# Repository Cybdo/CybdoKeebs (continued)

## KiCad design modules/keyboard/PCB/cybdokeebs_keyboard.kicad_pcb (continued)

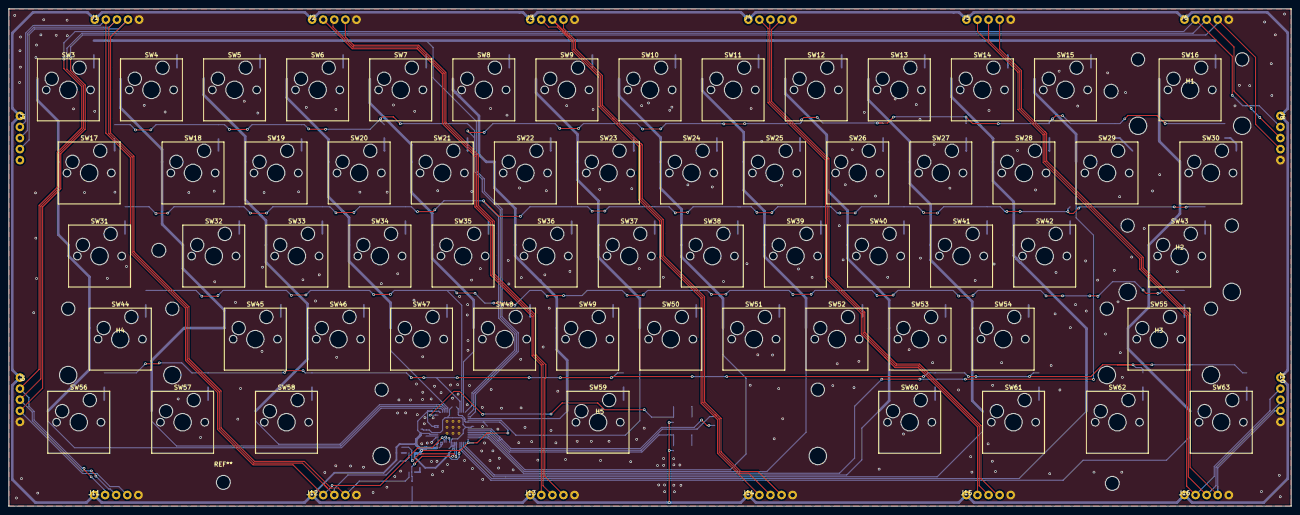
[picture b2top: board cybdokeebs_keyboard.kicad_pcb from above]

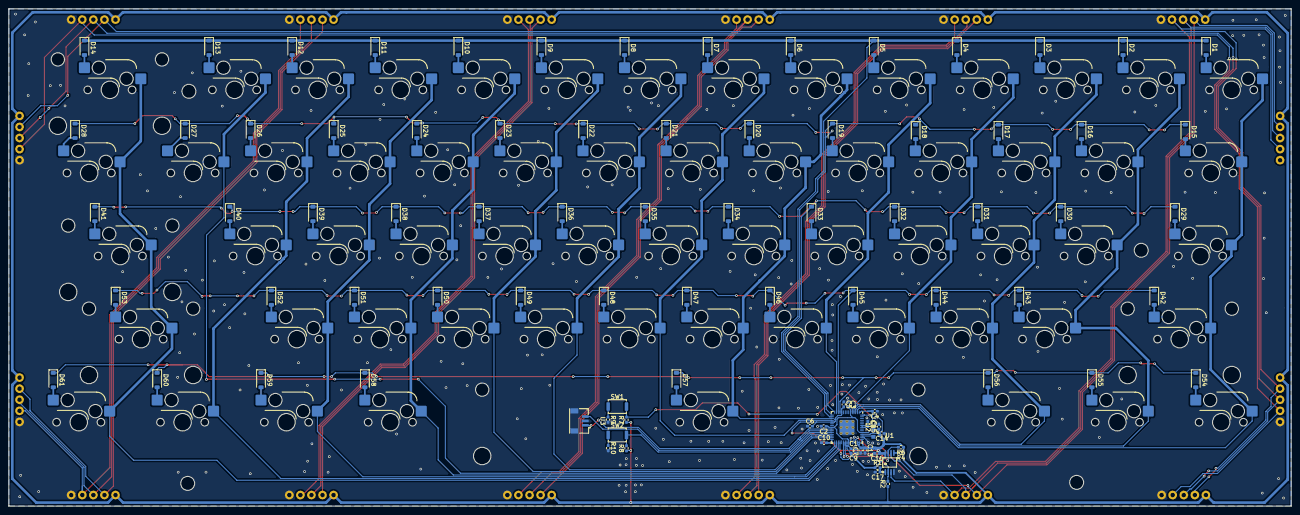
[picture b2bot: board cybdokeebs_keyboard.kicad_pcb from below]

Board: 2 copper layers, 294.0 x 114.0 mm, 172 parts (90 on the bottom side), 112 nets.

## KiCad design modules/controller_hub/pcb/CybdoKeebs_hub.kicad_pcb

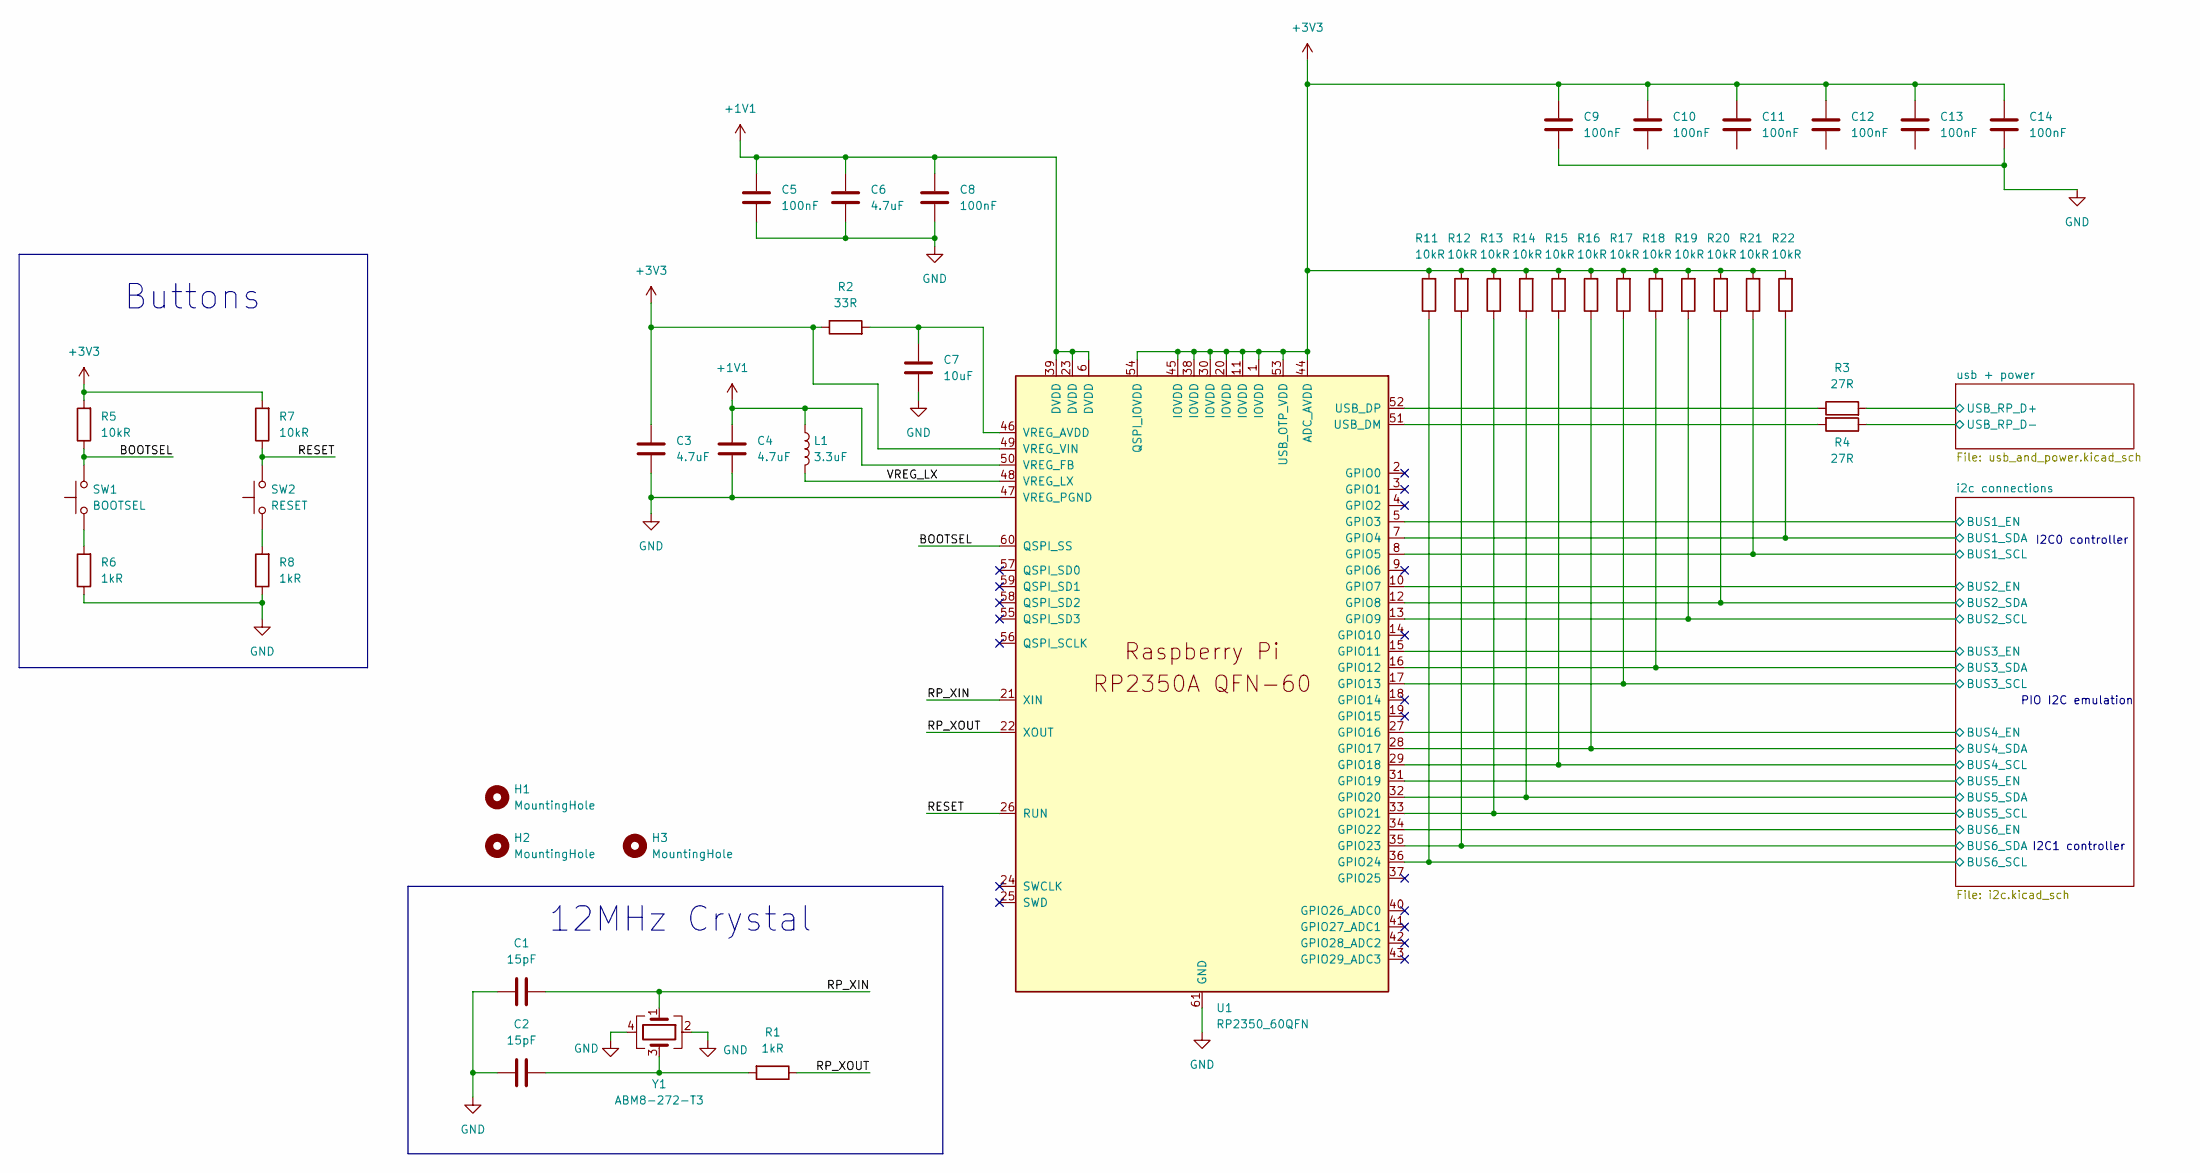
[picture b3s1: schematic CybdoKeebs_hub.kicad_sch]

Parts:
C1, C2: 15pF; C_0402_1005Metric_Pad0.74x0.62mm_HandSolder
C3, C4, C6: 4.7uF; C_0402_1005Metric_Pad0.74x0.62mm_HandSolder
C5, C8, C9, C10, C11, C12, C13, C14: 100nF; C_0402_1005Metric_Pad0.74x0.62mm_HandSolder
C7: 10uF; C_0402_1005Metric_Pad0.74x0.62mm_HandSolder
H1, H2, H3: MountingHole; MountingHole_3.2mm_M3
L1: 3.3uF; INDC1608X95N
R1, R6, R8: 1kR; R_0402_1005Metric_Pad0.72x0.64mm_HandSolder
R2: 33R; R_0402_1005Metric_Pad0.72x0.64mm_HandSolder
R3, R4: 27R; R_0402_1005Metric_Pad0.72x0.64mm_HandSolder
R5, R7, R11, R12, R13, R14, R15, R16, R17, R18, R19, R20, R21, R22: 10kR; R_0402_1005Metric_Pad0.72x0.64mm_HandSolder
SW1: BOOTSEL; SW_Push_SPST_NO_Alps_SKRK
SW2: RESET; SW_Push_SPST_NO_Alps_SKRK
U1: RP2350_60QFN; RP2350-QFN-60-1EP_7x7_P0.4mm_EP3.4x3.4mm_ThermalVias
Y1: ABM8-272-T3; Crystal_SMD_Abracon_ABM8G-4Pin_3.2x2.5mm

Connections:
+1V1: C4.1, C5.1, C6.1, C8.1, L1.1, U1.6 (DVDD), U1.23 (DVDD), U1.39 (DVDD), U1.50 (VREG_FB)
+3V3: C3.1, C9.1, C10.1, C11.1, C12.1, C13.1, C14.1, R2.1, R5.2, R7.2, R11.2, R12.2, R13.2, R14.2, R15.2, R16.2, R17.2, R18.2, R19.2, R20.2, R21.2, R22.2, U1.1 (IOVDD), U1.11 (IOVDD), U1.20 (IOVDD), U1.30 (IOVDD), U1.38 (IOVDD), U1.44 (ADC_AVDD), U1.45 (IOVDD), U1.49 (VREG_VIN), U1.53 (USB_OTP_VDD), U1.54 (QSPI_IOVDD); also elsewhere on the board
/BOOTSEL: R5.1, SW1.2, U1.60 (QSPI_SS)
/RESET: R7.1, SW2.2, U1.26 (RUN)
/RP_XIN: C1.2, U1.21 (XIN), Y1.1
/RP_XOUT: R1.1, U1.22 (XOUT)
/VREG_LX: L1.2, U1.48 (VREG_LX)
/i2c connections/BUS1_EN: U1.5 (GPIO3); also elsewhere on the board
/i2c connections/BUS1_SCL: R21.1, U1.8 (GPIO5); also elsewhere on the board
/i2c connections/BUS1_SDA: R22.1, U1.7 (GPIO4); also elsewhere on the board
/i2c connections/BUS2_EN: U1.10 (GPIO7); also elsewhere on the board
/i2c connections/BUS2_SCL: R19.1, U1.13 (GPIO9); also elsewhere on the board
/i2c connections/BUS2_SDA: R20.1, U1.12 (GPIO8); also elsewhere on the board
/i2c connections/BUS3_EN: U1.15 (GPIO11); also elsewhere on the board
/i2c connections/BUS3_SCL: R17.1, U1.17 (GPIO13); also elsewhere on the board
/i2c connections/BUS3_SDA: R18.1, U1.16 (GPIO12); also elsewhere on the board
/i2c connections/BUS4_EN: U1.27 (GPIO16); also elsewhere on the board
/i2c connections/BUS4_SCL: R15.1, U1.29 (GPIO18); also elsewhere on the board
/i2c connections/BUS4_SDA: R16.1, U1.28 (GPIO17); also elsewhere on the board
/i2c connections/BUS5_EN: U1.31 (GPIO19); also elsewhere on the board
/i2c connections/BUS5_SCL: R13.1, U1.33 (GPIO21); also elsewhere on the board
/i2c connections/BUS5_SDA: R14.1, U1.32 (GPIO20); also elsewhere on the board
/i2c connections/BUS6_EN: U1.34 (GPIO22); also elsewhere on the board
/i2c connections/BUS6_SCL: R11.1, U1.36 (GPIO24); also elsewhere on the board
/i2c connections/BUS6_SDA: R12.1, U1.35 (GPIO23); also elsewhere on the board
/usb + power/USB_RP_D+: R3.2; also elsewhere on the board
/usb + power/USB_RP_D-: R4.1; also elsewhere on the board
GND: C1.1, C2.1, C3.2, C4.2, C5.2, C6.2, C7.2, C8.2, C9.2, C14.2, R6.1, R8.1, U1.47 (VREG_PGND), U1.61 (GND), Y1.2, Y1.4; also elsewhere on the board
unnamed: C2.2, R1.2, Y1.3
unnamed: R6.2, SW1.1
unnamed: R8.2, SW2.1
unnamed: R4.2, U1.51 (USB_DM)
unnamed: R3.1, U1.52 (USB_DP)
unnamed: C7.1, R2.2, U1.46 (VREG_AVDD)

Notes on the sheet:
PIO I2C emulation
I2C0 controller
I2C1 controller
Buttons
12MHz Crystal

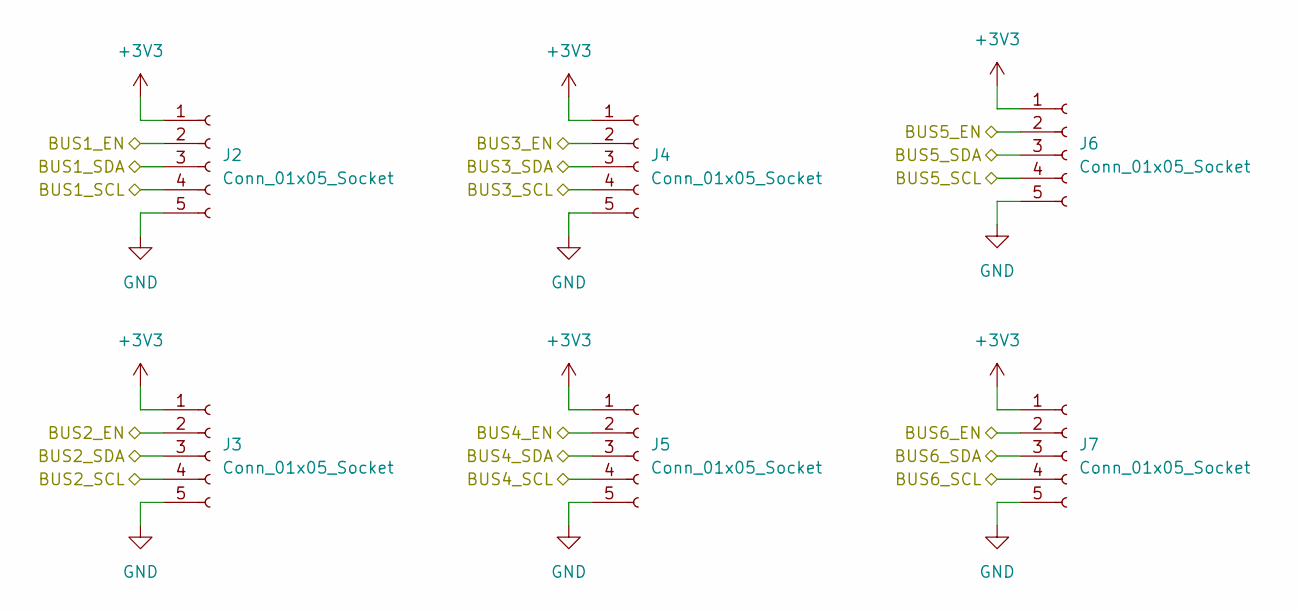
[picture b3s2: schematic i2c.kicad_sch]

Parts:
J2, J3, J4, J5, J6, J7: Conn_01x05_Socket; pogo 5pin 2.54

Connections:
+3V3: J2.1, J3.1, J4.1, J5.1, J6.1, J7.1; also elsewhere on the board
/i2c connections/BUS1_EN: J2.2; also elsewhere on the board
/i2c connections/BUS1_SCL: J2.4; also elsewhere on the board
/i2c connections/BUS1_SDA: J2.3; also elsewhere on the board
/i2c connections/BUS2_EN: J3.2; also elsewhere on the board
/i2c connections/BUS2_SCL: J3.4; also elsewhere on the board
/i2c connections/BUS2_SDA: J3.3; also elsewhere on the board
/i2c connections/BUS3_EN: J4.2; also elsewhere on the board
/i2c connections/BUS3_SCL: J4.4; also elsewhere on the board
/i2c connections/BUS3_SDA: J4.3; also elsewhere on the board
/i2c connections/BUS4_EN: J5.2; also elsewhere on the board
/i2c connections/BUS4_SCL: J5.4; also elsewhere on the board
/i2c connections/BUS4_SDA: J5.3; also elsewhere on the board
/i2c connections/BUS5_EN: J6.2; also elsewhere on the board
/i2c connections/BUS5_SCL: J6.4; also elsewhere on the board
/i2c connections/BUS5_SDA: J6.3; also elsewhere on the board
/i2c connections/BUS6_EN: J7.2; also elsewhere on the board
/i2c connections/BUS6_SCL: J7.4; also elsewhere on the board
/i2c connections/BUS6_SDA: J7.3; also elsewhere on the board
GND: J2.5, J3.5, J4.5, J5.5, J6.5, J7.5; also elsewhere on the board

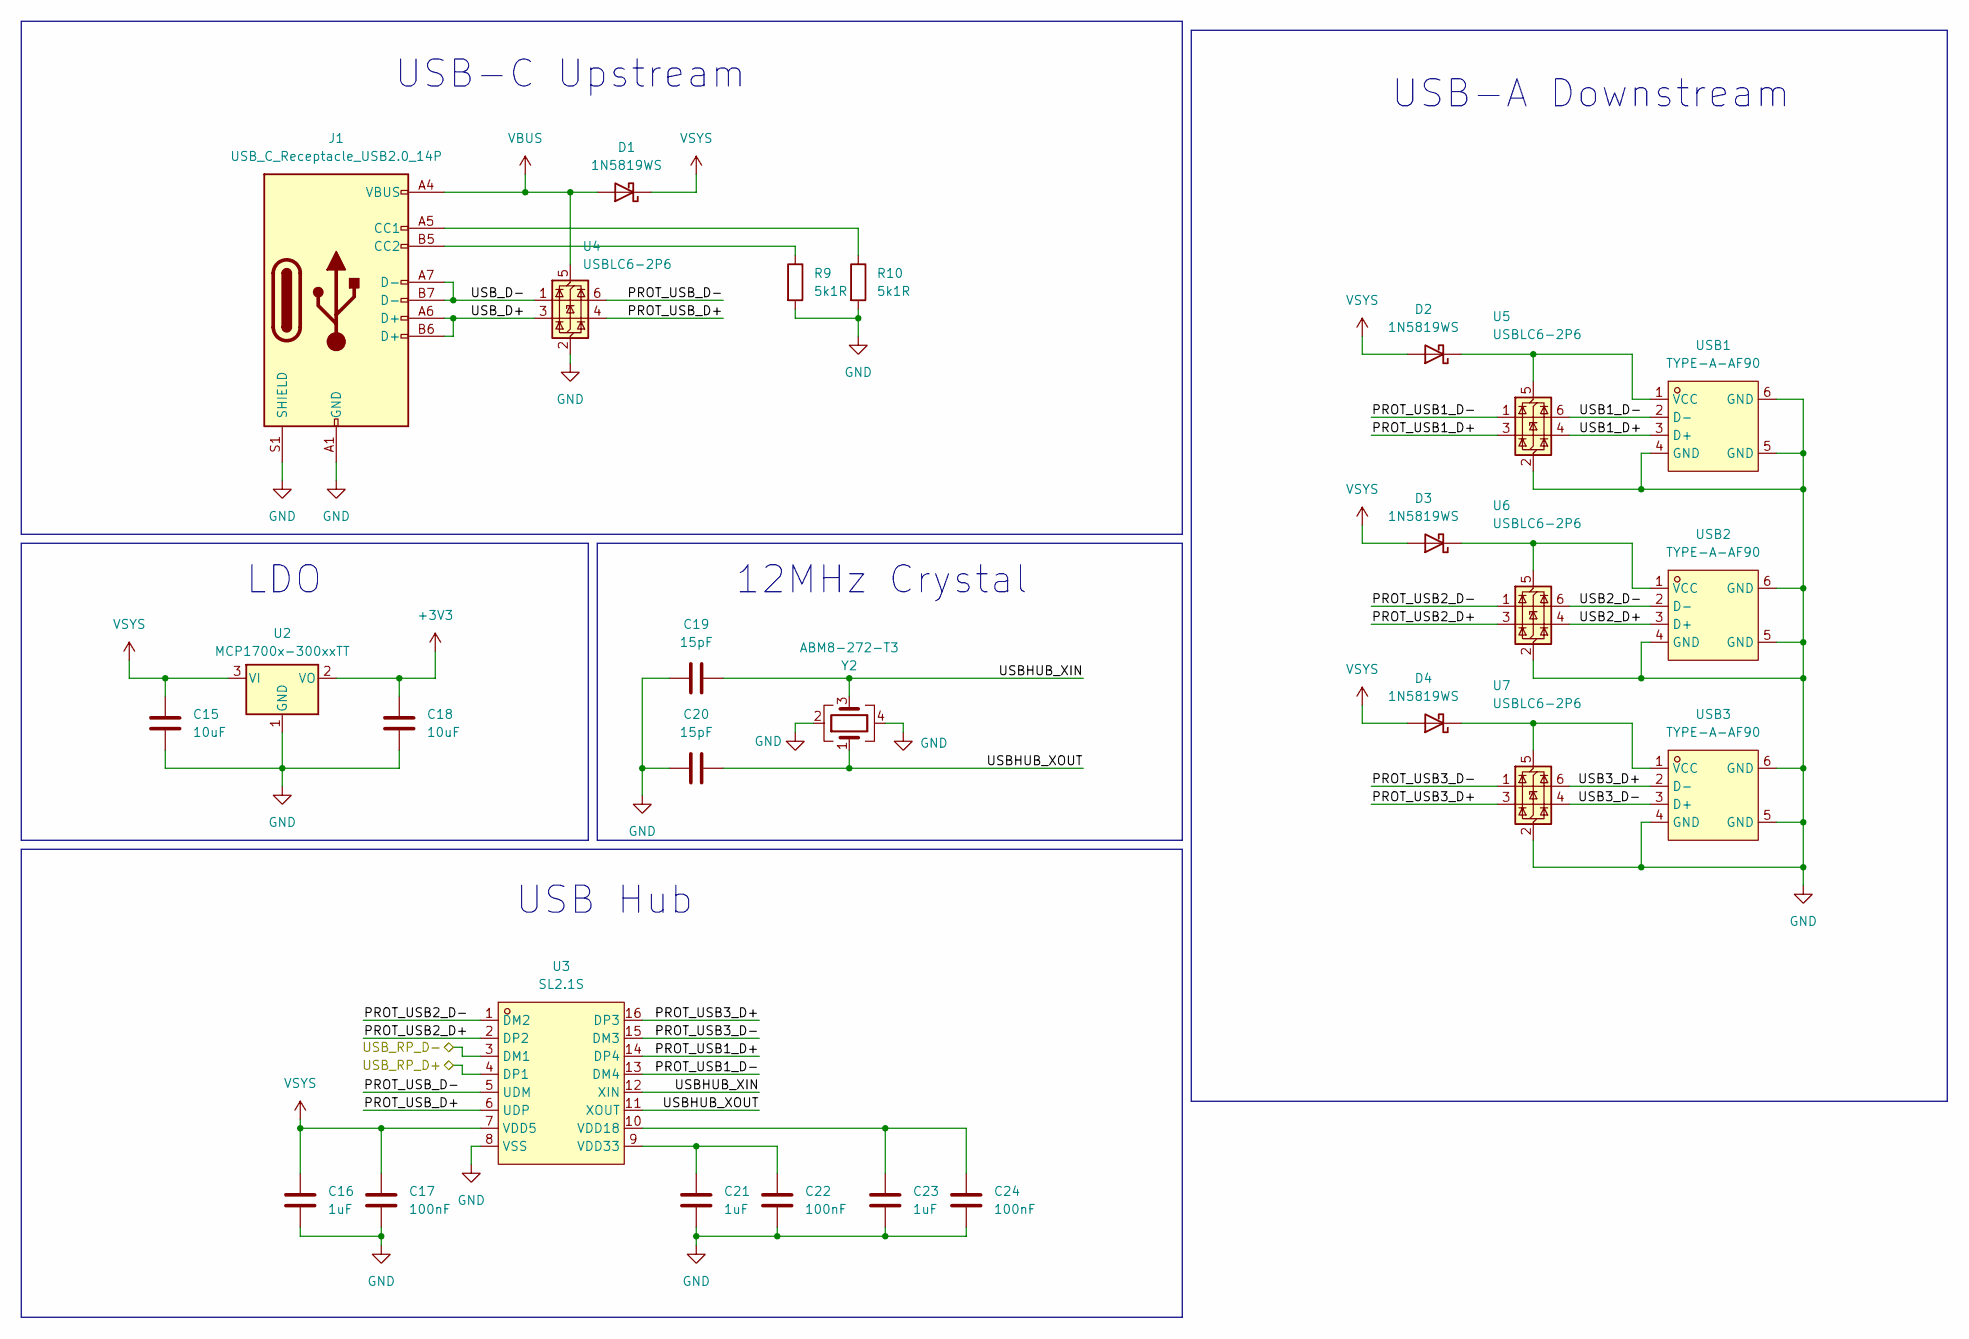
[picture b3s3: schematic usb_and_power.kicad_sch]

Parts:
C15, C18: 10uF; C_0402_1005Metric_Pad0.74x0.62mm_HandSolder
C16, C21, C23: 1uF; C_0402_1005Metric_Pad0.74x0.62mm_HandSolder
C17, C22, C24: 100nF; C_0402_1005Metric_Pad0.74x0.62mm_HandSolder
C19, C20: 15pF; C_0402_1005Metric_Pad0.74x0.62mm_HandSolder
D1, D2, D3, D4: 1N5819WS; D_SOD-323
J1: USB_C_Receptacle_USB2.0_14P; USB_C_Receptacle_HRO_TYPE-C-31-M-12
R9, R10: 5k1R; R_0402_1005Metric_Pad0.72x0.64mm_HandSolder
U2: MCP1700x-300xxTT; SOT-23
U3: SL2.1S; SSOP-16_L4.6-W2.6-P0.53-LS4.0-BL; MPN SL2.1s; LCSC Part C2684433
U4, U5, U6, U7: USBLC6-2P6; SOT-666
USB1, USB2, USB3: TYPE-A-AF90; USB-A-TH_U-A-24DD-Y-13; MPN Type-A-AF90; LCSC Part C53207796
Y2: ABM8-272-T3; Crystal_SMD_Abracon_ABM8G-4Pin_3.2x2.5mm

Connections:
+3V3: C18.1, U2.2 (VO); also elsewhere on the board
/usb + power/PROT_USB1_D+: U3.14 (DP4), U5.3 (I/O2)
/usb + power/PROT_USB1_D-: U3.13 (DM4), U5.1 (I/O1)
/usb + power/PROT_USB2_D+: U3.2 (DP2), U6.3 (I/O2)
/usb + power/PROT_USB2_D-: U3.1 (DM2), U6.1 (I/O1)
/usb + power/PROT_USB3_D+: U3.16 (DP3), U7.3 (I/O2)
/usb + power/PROT_USB3_D-: U3.15 (DM3), U7.1 (I/O1)
/usb + power/PROT_USB_D+: U3.6 (UDP), U4.4 (I/O2)
/usb + power/PROT_USB_D-: U3.5 (UDM), U4.6 (I/O1)
/usb + power/USB1_D+: U5.4 (I/O2), USB1.3 (D+)
/usb + power/USB1_D-: U5.6 (I/O1), USB1.2 (D-)
/usb + power/USB2_D+: U6.4 (I/O2), USB2.3 (D+)
/usb + power/USB2_D-: U6.6 (I/O1), USB2.2 (D-)
/usb + power/USB3_D+: U7.6 (I/O1), USB3.2 (D-)
/usb + power/USB3_D-: U7.4 (I/O2), USB3.3 (D+)
/usb + power/USBHUB_XIN: C19.2, U3.12 (XIN), Y2.3
/usb + power/USBHUB_XOUT: C20.2, U3.11 (XOUT), Y2.1
/usb + power/USB_D+: J1.A6 (D+), J1.B6 (D+), U4.3 (I/O2)
/usb + power/USB_D-: J1.A7 (D-), J1.B7 (D-), U4.1 (I/O1)
/usb + power/USB_RP_D+: U3.4 (DP1); also elsewhere on the board
/usb + power/USB_RP_D-: U3.3 (DM1); also elsewhere on the board
GND: C15.2, C16.2, C17.2, C18.2, C19.1, C20.1, C21.2, C22.2, C23.2, C24.2, J1.A1 (GND), J1.A12 (GND), J1.B1 (GND), J1.B12 (GND), J1.S1 (SHIELD), R9.2, R10.2, U2.1 (GND), U3.8 (VSS), U4.2 (GND), U5.2 (GND), U6.2 (GND), U7.2 (GND), USB1.4 (GND), USB1.5 (GND), USB1.6 (GND), USB2.4 (GND), USB2.5 (GND), USB2.6 (GND), USB3.4 (GND), USB3.5 (GND), USB3.6 (GND), Y2.2, Y2.4; also elsewhere on the board
unnamed: D2.1 (K), U5.5 (VBUS), USB1.1 (VCC)
unnamed: D3.1 (K), U6.5 (VBUS), USB2.1 (VCC)
unnamed: D4.1 (K), U7.5 (VBUS), USB3.1 (VCC)
unnamed: J1.A5 (CC1), R10.1
unnamed: J1.B5 (CC2), R9.1
unnamed: C23.1, C24.1, U3.10 (VDD18)
unnamed: C21.1, C22.1, U3.9 (VDD33)
VBUS: D1.2 (A), J1.A4 (VBUS), J1.A9 (VBUS), J1.B4 (VBUS), J1.B9 (VBUS), U4.5 (VBUS)
VSYS: C15.1, C16.1, C17.1, D1.1 (K), D2.2 (A), D3.2 (A), D4.2 (A), U2.3 (VI), U3.7 (VDD5)

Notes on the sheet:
LDO
USB-C Upstream
USB Hub
12MHz Crystal
USB-A Downstream

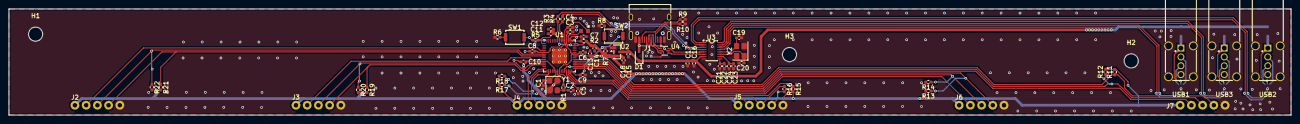
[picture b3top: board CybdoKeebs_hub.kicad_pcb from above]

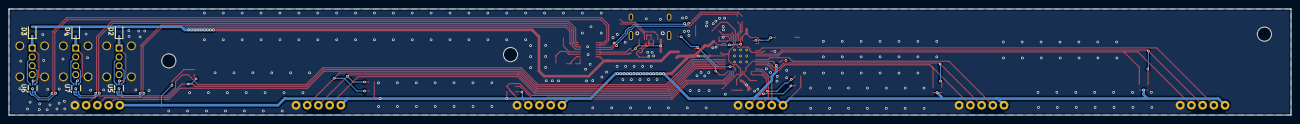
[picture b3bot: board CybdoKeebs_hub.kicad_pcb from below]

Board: 2 copper layers, 290.0 x 24.0 mm, 75 parts (6 on the bottom side), 61 nets.

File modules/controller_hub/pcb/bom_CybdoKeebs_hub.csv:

"Id","Designator","Footprint","Quantity","Designation","Supplier and ref",
1,"C1, C2, C19, C20","C_0402_1005Metric_Pad0.74x0.62mm_HandSolder",4,"15pF",,,
2,"C3, C4, C6","C_0402_1005Metric_Pad0.74x0.62mm_HandSolder",3,"4.7uF",,,
3,"C5, C8, C9, C10, C11, C12, C13, C14, C17, C22, C24","C_0402_1005Metric_Pad0.74x0.62mm_HandSolder",11,"100nF",,,
4,"C7, C15, C18","C_0402_1005Metric_Pad0.74x0.62mm_HandSolder",3,"10uF",,,
5,"C16, C21, C23","C_0402_1005Metric_Pad0.74x0.62mm_HandSolder",3,"1uF",,,
6,"D1, D2, D3, D4","D_SOD-323",4,"1N5819WS",,,
7,"J1","USB_C_Receptacle_HRO_TYPE-C-31-M-12",1,"USB_C_Receptacle_USB2.0_14P",,,
8,"J2, J3, J4, J5, J6, J7","pogo 5pin 2.54",6,"Conn_01x05_Socket",,,
9,"L1","INDC1608X95N",1,"3.3uF",,,
10,"R1, R6, R8","R_0402_1005Metric_Pad0.72x0.64mm_HandSolder",3,"1kR",,,
11,"R2","R_0402_1005Metric_Pad0.72x0.64mm_HandSolder",1,"33R",,,
12,"R3, R4","R_0402_1005Metric_Pad0.72x0.64mm_HandSolder",2,"27R",,,
13,"R5, R7, R11, R12, R13, R14, R15, R16, R17, R18, R19, R20, R21, R22","R_0402_1005Metric_Pad0.72x0.64mm_HandSolder",14,"10kR",,,
14,"R9, R10","R_0402_1005Metric_Pad0.72x0.64mm_HandSolder",2,"5k1R",,,
15,"SW1","SW_Push_SPST_NO_Alps_SKRK",1,"BOOTSEL",,,
16,"SW2","SW_Push_SPST_NO_Alps_SKRK",1,"RESET",,,
17,"U1","RP2350-QFN-60-1EP_7x7_P0.4mm_EP3.4x3.4mm_ThermalVias",1,"RP2350_60QFN",,,
18,"U2","SOT-23",1,"MCP1700x-300xxTT",,,
19,"U3","SSOP-16_L4.6-W2.6-P0.53-LS4.0-BL",1,"SL2.1S",,,
20,"U4, U5, U6, U7","SOT-666",4,"USBLC6-2P6",,,
21,"USB1, USB2, USB3","USB-A-TH_U-A-24DD-Y-13",3,"TYPE-A-AF90",,,
22,"Y1, Y2","Crystal_SMD_Abracon_ABM8G-4Pin_3.2x2.5mm",2,"ABM8-272-T3",,,

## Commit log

2026-04-23 started on control hub
2026-04-25 finish minimum system, add i2c connectors
2026-04-28 add template for each module
2026-06-12 hub done, started macropad
2026-06-20 macropad finished
2026-06-20 started main keyboard
2026-06-21 kb mostly done
2026-06-21 finished all pcbs
2026-06-21 zine!! and cases
2026-06-21 ship ship ship!!!
2026-06-23 oops forgor assembly step
2026-06-23 git lfs
2026-06-23 macropad holes line up now
    not updated in assembly.step but they line up now
2026-06-24 updated BOM to include hub-specific components
2026-06-25 updates stuffs
2026-06-25 update zine, add 3d screenshots
2026-06-27 new case and cads
2026-06-27 polish up cad
2026-06-27 typo
